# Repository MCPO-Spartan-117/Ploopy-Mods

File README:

# Ploopy Mods
This repo is a collection of [Ploopy Mouse](https://github.com/ploopyco) Kicad Conversions, PCB Replacements and mods.
You can visit their [store page here](https://ploopy.co) and the [firmware here](https://github.com/qmk/qmk_firmware) or their [website here](https://qmk.fm).

## Currently has mods for:
K = Kicad Conversions
P = PCB Replacements
M = Mods
P+M = PCB Replacement only Mods

[Ploopy Thumb Trackball](https://github.com/ploopyco/thumb-trackball): P

## Directories:
Models: A directory for 3D models made from or for either Kicad or Freecad
PCBs: Where kicad PCBs are stored
Printables: Models you are meant to print
Project-files: Global directory for Kicad symbols and footprints

## TODO:
* Rotary Encoder version + Lighter scroll wheel
* Rework optical sensor version
* (Full?) hall effect sensor version
* D2FC switches version?
* Ribbion cable/cabled version?
* Seperated/PCBless design
* Remake BTUs
* 3-4mm BTUs?
* PTFE BTUs?
* Port to other Ploopies
* Port to other PCB Manufacturers
* (Handsolderable?) LEDs?
* Port originals to kicad?
* Convert originals to ARM?

## Contributions
You want to help checking off the todo list, make mods of your own and submit them or think you can make a existing mod better?
You can make a [pull request](https://docs.github.com/en/pull-requests/collaborating-with-pull-requests/proposing-changes-to-your-work-with-pull-requests/creating-a-pull-request) detailing what you are doing and we'll look over it.

However please use [Kicad for PCBs](https://www.kicad.org) or [Freecad for Models](https://www.freecad.org) and use their native formats, they are open source, free and easily obtainable, using other CADs and/or formats will make it harder to work with and we may outright reject them because of this.

## Kicad Instructions
* Use the [Archive 3D Models Plugin](https://github.com/MitjaNemec/Archive3DModels) for Kicad with the default path.
* Make relative symlinks named Project-files and packages3D to Project-files and Models/Kicad respectively in your PCB project directory, it will keep all the symbols, footprint and 3D models in one place to make it easily transportable, example in PCBs/JLCPCB/Thumb-v1.

## Freecad Instructions
* Nothing atm.

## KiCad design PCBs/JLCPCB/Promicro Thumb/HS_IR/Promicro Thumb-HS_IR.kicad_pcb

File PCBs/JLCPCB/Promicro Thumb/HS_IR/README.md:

# Promicro Thumb-HS_IR
## WARNING, THIS BOARD IS MEANT FOR A 3.3V BOARD, THE SENSOR WON'T WORK AS IT ONLY HAS A REGULATOR FOR 3.3V to 1.8V FOR THE LED, NOT THE SENSOR'S 3.3V!!!

This PCB is designed to offload all the processing to a 3.3V Promicro sized/pinout board, so we can work with a 2 layer board and we can replace the processing board with a better/more functioning one if we want to.  
We intentionally didn't use the USB VBUS directly for components as we wanted to be able to support wireless [ZMK](https://zmk.dev) boards when it gets support for mouse APIs and we have a place where you can install a battery and switch.

These boards don't use a ESD component as it's on the MCU board.

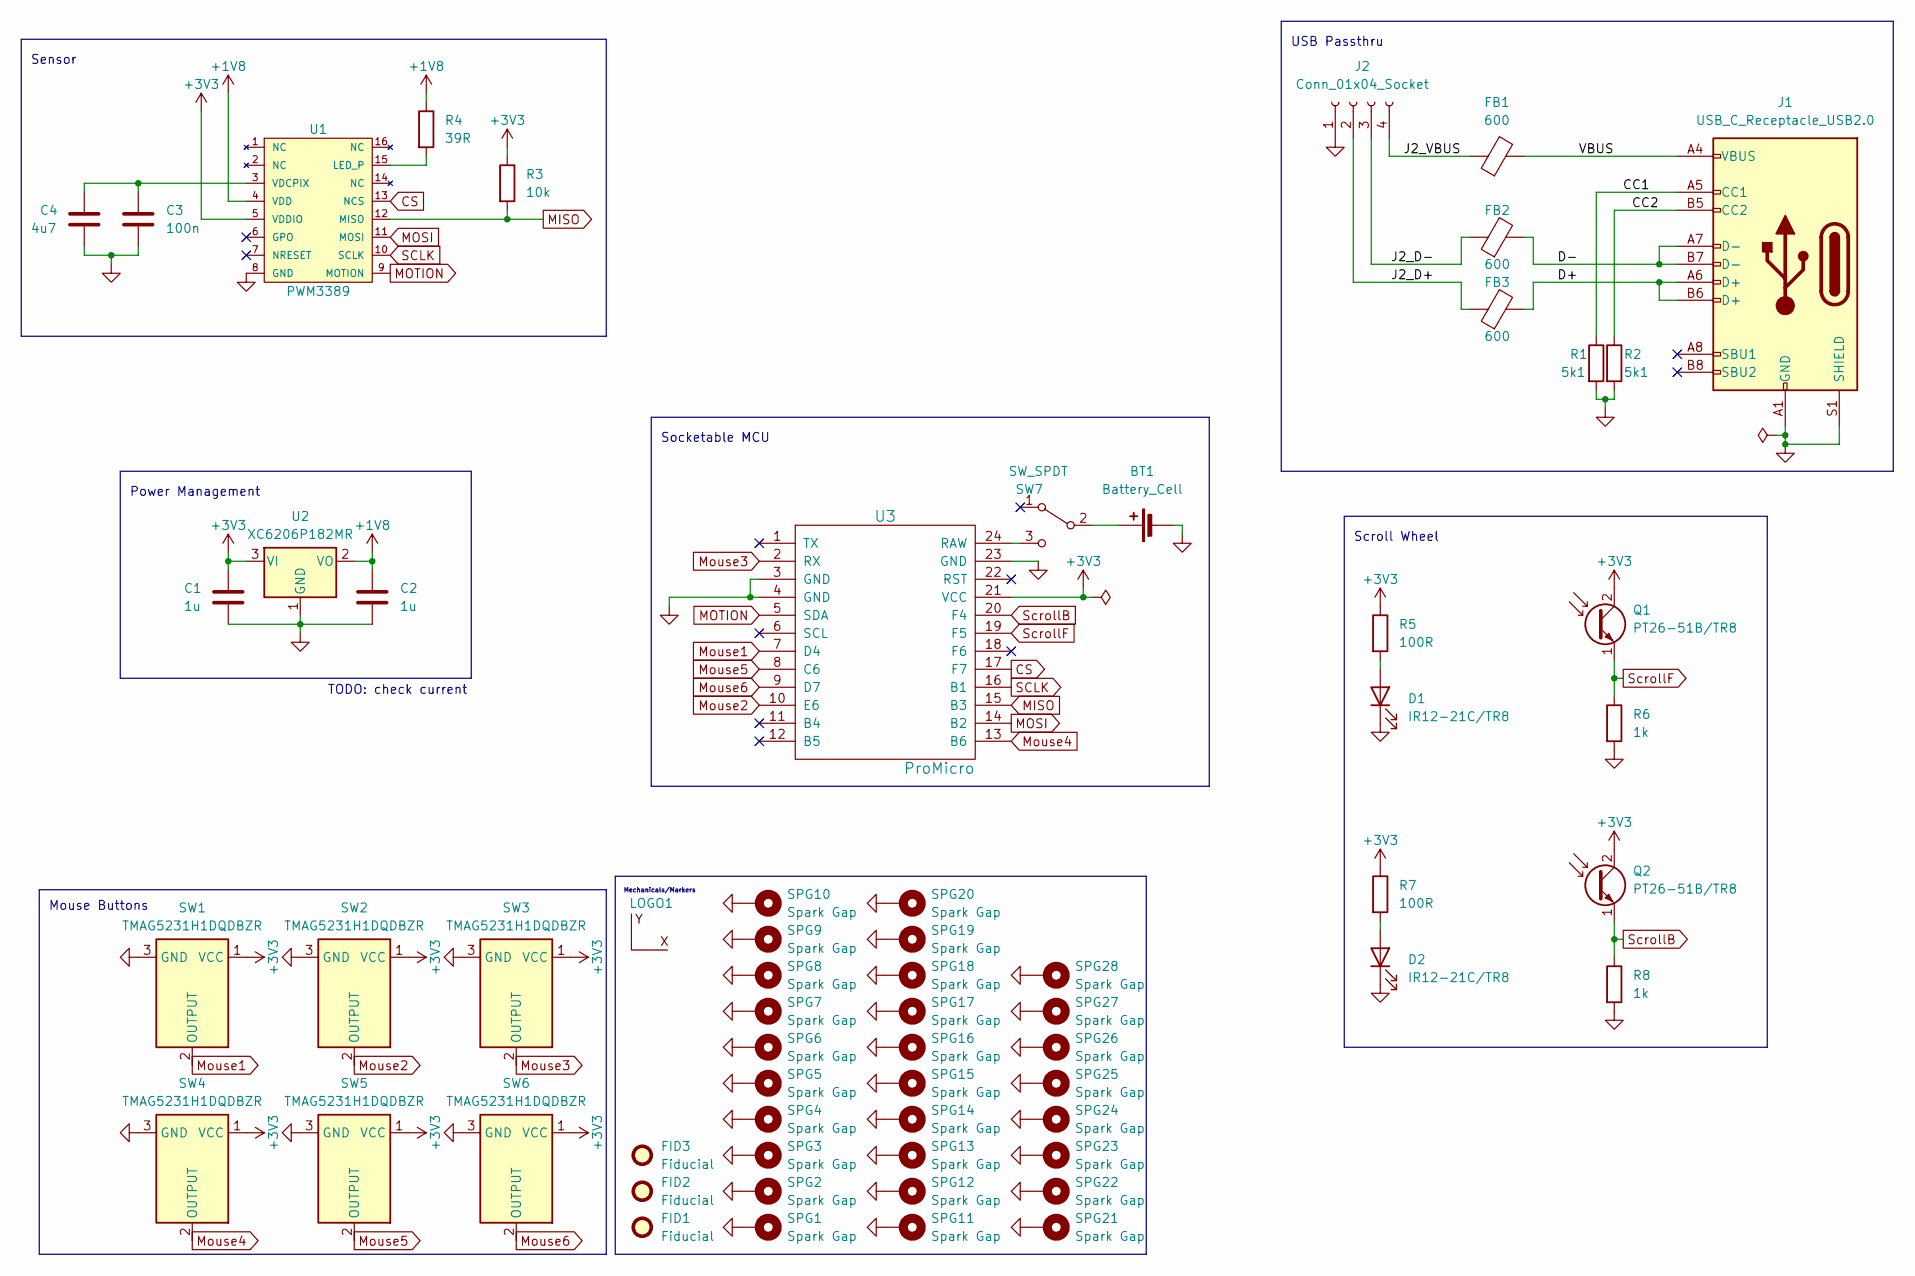
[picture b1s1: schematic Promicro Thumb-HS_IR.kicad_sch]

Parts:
BT1: Battery_Cell; Battery_pads_reversible
C1, C2: 1u; C_0805_2012Metric
C3: 100n; C_0805_2012Metric
C4: 4u7; C_0805_2012Metric
D1, D2: IR12-21C/TR8; IR12-21C_TR8
FB1, FB2, FB3: 600; R_0805_2012Metric
FID1, FID2, FID3: Fiducial; Fiducial_0.5mm_Mask1mm
J1: USB_C_Receptacle_USB2.0; USB_C_Receptacle_G-Switch_GT-USB-7010ASV
J2: Conn_01x04_Socket; PinHeader_1x04_P2.54mm_Vertical
LOGO1: Coordinate System-Ploopy
Q1, Q2: PT26-51B/TR8; PT26-51B_TR8
R1, R2: 5k1; R_0805_2012Metric
R3: 10k; R_0805_2012Metric
R4: 39R; R_0805_2012Metric
R5, R7: 100R; R_0805_2012Metric
R6, R8: 1k; R_0805_2012Metric
SPG1, SPG2, SPG3, SPG4, SPG5, SPG6, SPG7, SPG8, SPG9, SPG10, SPG11, SPG12, SPG13, SPG14, SPG15, SPG16, SPG17, SPG18, SPG19, SPG20, SPG21, SPG22, SPG23, SPG24, SPG25, SPG26, SPG27, SPG28: Spark Gap; SparkGap
SW1, SW2, SW3, SW4, SW5, SW6: TMAG5231H1DQDBZR; SOT-23
SW7: SW_SPDT; SW_SPDT_PCM12
U1: PWM3389; PMW3360DM-T2QU
U2: XC6206P182MR; SOT-23-3
U3: ProMicro

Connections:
+1V8: C2.1, R4.1, U1.4 (VDD), U2.2 (VO)
+3V3: C1.1, Q1.2 (C), Q2.2 (C), R3.1, R5.1, R7.1, SW1.1 (VCC), SW2.1 (VCC), SW3.1 (VCC), SW4.1 (VCC), SW5.1 (VCC), SW6.1 (VCC), U1.5 (VDDIO), U2.3 (VI), U3.21 (VCC)
/CC1: J1.A5 (CC1), R1.1
/CC2: J1.B5 (CC2), R2.1
/D+: FB3.2, J1.A6 (D+), J1.B6 (D+)
/D-: FB2.2, J1.A7 (D-), J1.B7 (D-)
/J2_D+: FB3.1, J2.2
/J2_D-: FB2.1, J2.3
/J2_VBUS: FB1.1, J2.4
/VBUS: FB1.2, J1.A4 (VBUS), J1.A9 (VBUS), J1.B4 (VBUS), J1.B9 (VBUS)
CS: U1.13 (NCS), U3.17 (F7)
GND: BT1.2 (-), C1.2, C2.2, C3.2, C4.2, D1.1 (K), D2.1 (K), J1.A1 (GND), J1.A12 (GND), J1.B1 (GND), J1.B12 (GND), J1.S1 (SHIELD), J2.1, R1.2, R2.2, R6.2, R8.2, SPG1.1, SPG2.1, SPG3.1, SPG4.1, SPG5.1, SPG6.1, SPG7.1, SPG8.1, SPG9.1, SPG10.1, SPG11.1, SPG12.1, SPG13.1, SPG14.1, SPG15.1, SPG16.1, SPG17.1, SPG18.1, SPG19.1, SPG20.1, SPG21.1, SPG22.1, SPG23.1, SPG24.1, SPG25.1, SPG26.1, SPG27.1, SPG28.1, SW1.3 (GND), SW2.3 (GND), SW3.3 (GND), SW4.3 (GND), SW5.3 (GND), SW6.3 (GND), U1.8 (GND), U2.1 (GND), U3.3 (GND), U3.4 (GND), U3.23 (GND)
MISO: R3.2, U1.12 (MISO), U3.15 (B3)
MOSI: U1.11 (MOSI), U3.14 (B2)
MOTION: U1.9 (MOTION), U3.5 (SDA)
Mouse1: SW1.2 (OUTPUT), U3.7 (D4)
Mouse2: SW2.2 (OUTPUT), U3.10 (E6)
Mouse3: SW3.2 (OUTPUT), U3.2 (RX)
Mouse4: SW4.2 (OUTPUT), U3.13 (B6)
Mouse5: SW5.2 (OUTPUT), U3.8 (C6)
Mouse6: SW6.2 (OUTPUT), U3.9 (D7)
unnamed: BT1.1 (+), SW7.2 (B)
unnamed: D1.2 (A), R5.2
unnamed: D2.2 (A), R7.2
unnamed: SW7.3 (C), U3.24 (RAW)
unnamed: R4.2, U1.15 (LED_P)
unnamed: C3.1, C4.1, U1.3 (VDCPIX)
SCLK: U1.10 (SCLK), U3.16 (B1)
ScrollB: Q2.1 (E), R8.1, U3.20 (F4)
ScrollF: Q1.1 (E), R6.1, U3.19 (F5)

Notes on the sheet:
Scroll Wheel
USB Passthru
Sensor
TODO: check current
Power Management
Mouse Buttons
Mechanicals/Markers
Socketable MCU

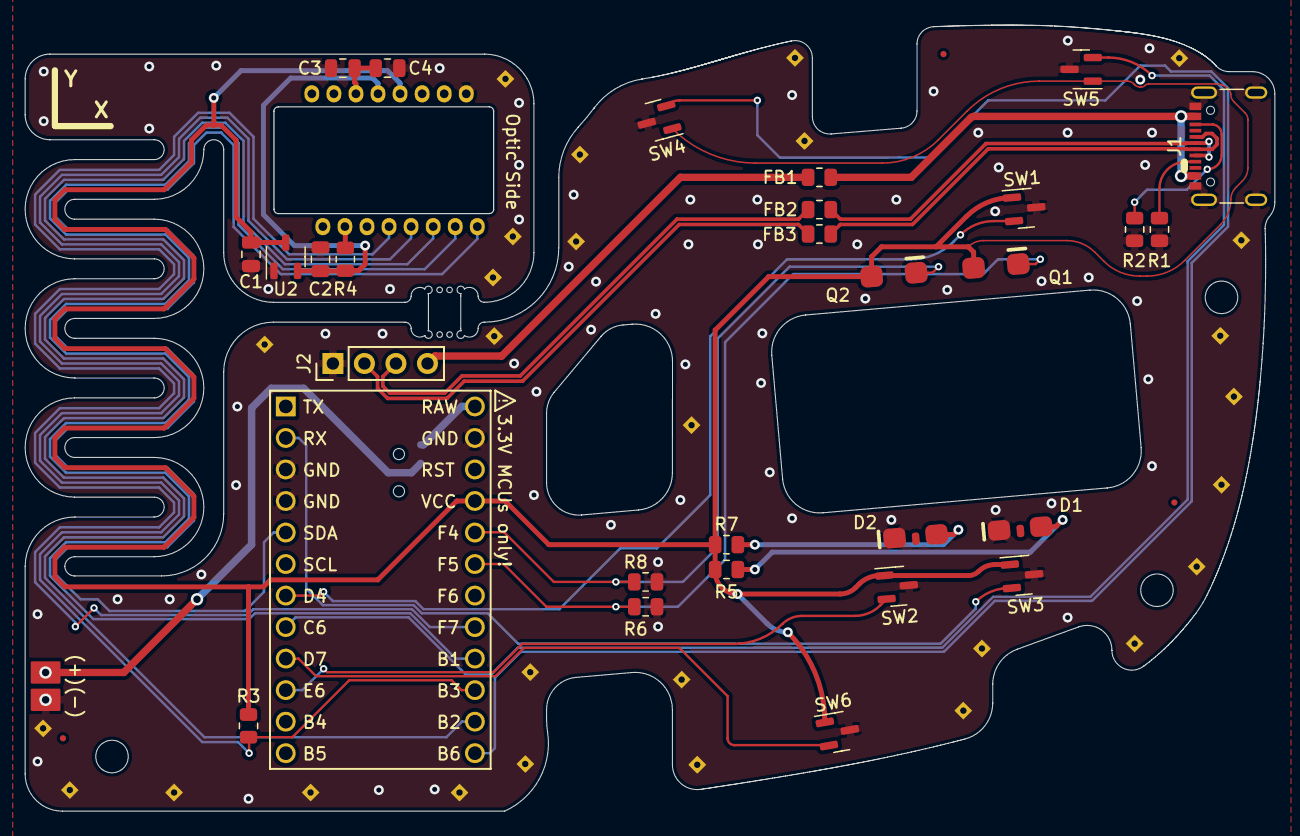
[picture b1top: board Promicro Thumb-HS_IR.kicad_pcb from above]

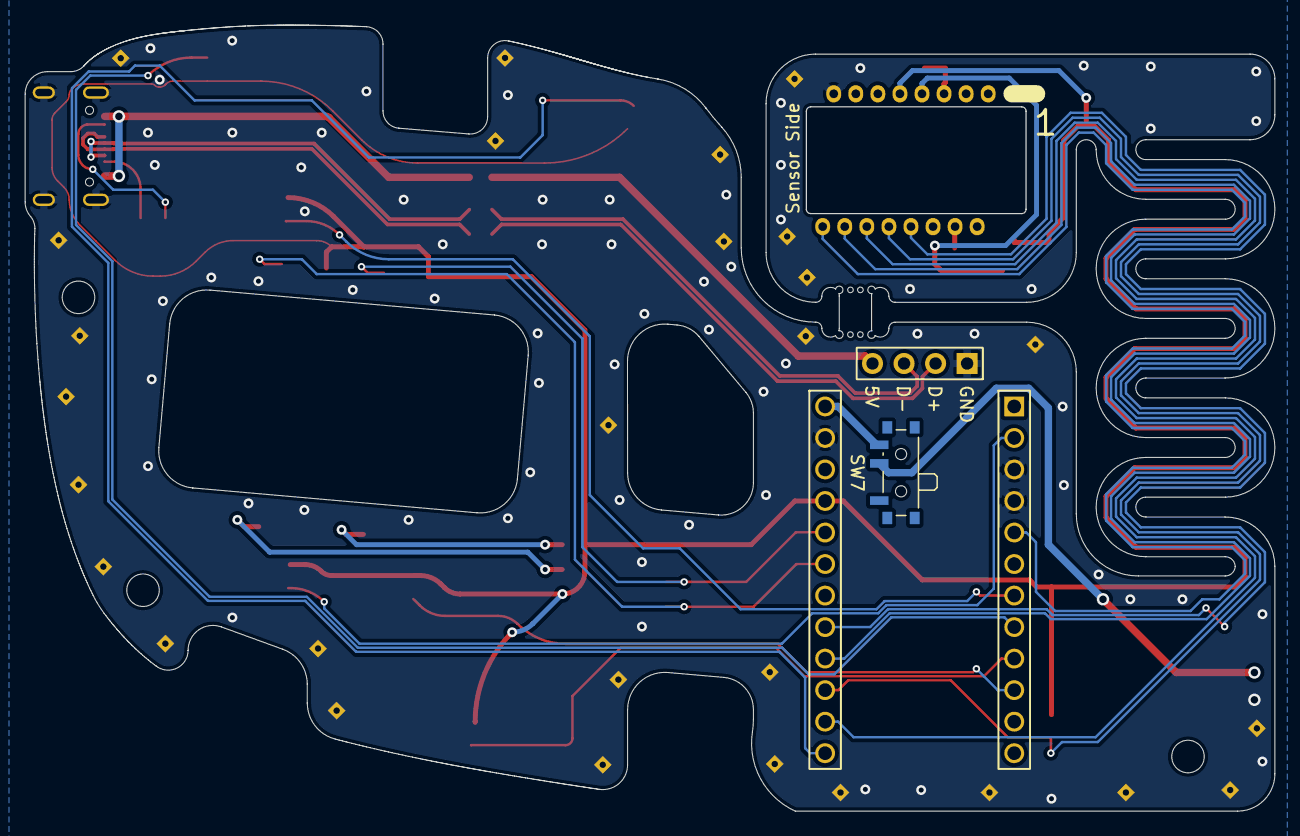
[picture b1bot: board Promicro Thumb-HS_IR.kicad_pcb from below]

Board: 2 copper layers, 100.7 x 63.3 mm, 64 parts (2 on the bottom side), 30 nets.

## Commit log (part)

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2024-03-17 Init
2024-03-17 Rename text files to appear as markdown
2024-03-17 Fixup Markdown Syntax
2024-03-18 Rename PCB, fix syntax and add .gitignore
2024-03-20 Add Hall Sensor version, more .gitignore and updated READMEs
2024-03-21 Smaller 3V3 tracks
